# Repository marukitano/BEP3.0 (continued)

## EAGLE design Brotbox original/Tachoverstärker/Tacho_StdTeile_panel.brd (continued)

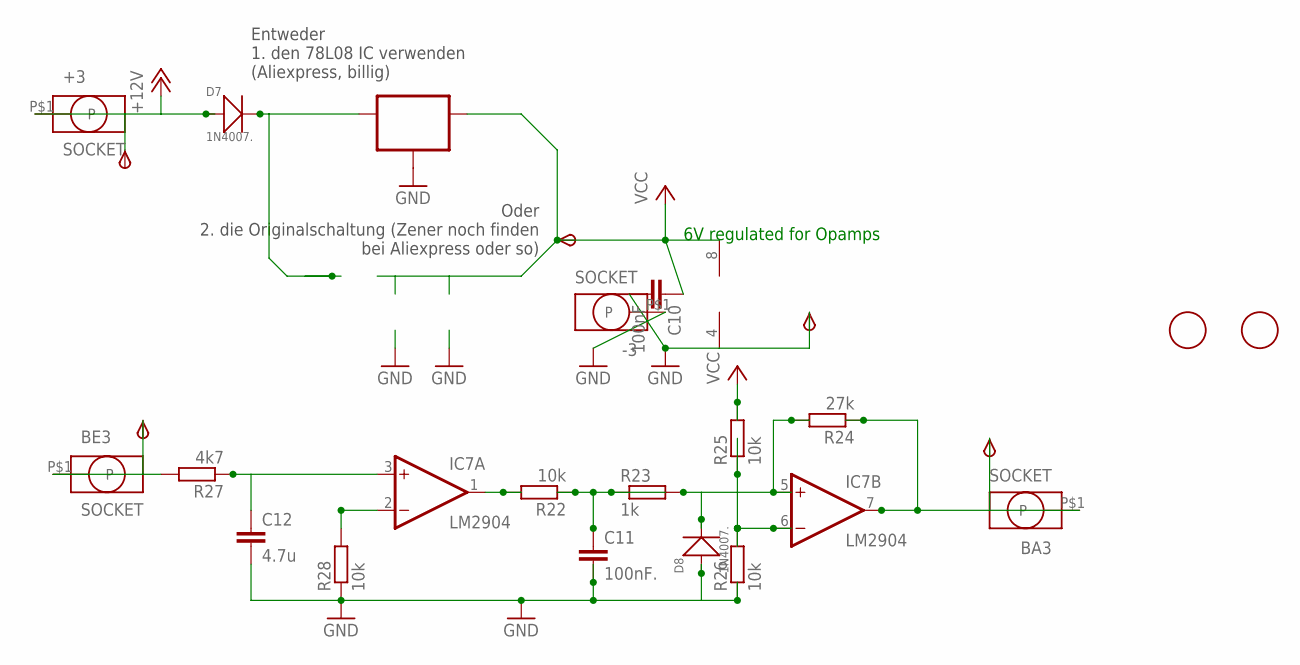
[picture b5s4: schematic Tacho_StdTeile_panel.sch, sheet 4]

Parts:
6V3: TPSB2.0; B2.0
+3: SOCKET; ID2.5MM
+12V3: TPSB2.0; B2.0
-3: SOCKET; ID2.5MM
AUS3: TPSB2.0; B2.0
BA3: SOCKET; ID2.5MM
BE3: SOCKET; ID2.5MM
C10: 100nF; C0805K
C11: 100nF.; C0805K
C12: 4.7u; C0805K
D7, D8: 1N4007.; DO-214AC
EIN3: TPSB2.0; B2.0
FID7, FID8: FIDUCIAL; FIDUCIAL_1MM
GND29: TPSB2.0; B2.0
IC7: LM2904; SO08
IC8: 78L06; SOT89_ROUND
R22, R25, R26, R28: 10k; R0805
R23: 1k; R0805
R24: 27k; R0805
R27: 4k7; R0805

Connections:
+12V: +3.P$1, +12V3.TP, D7.1 (+); also elsewhere on the board
+12V4: AUS3.TP, BA3.P$1, IC7.7 (OUT), R24.1
GND: -3.P$1, C10.2, C11.2, C12.2, D8.1 (+), GND29.TP, IC7.4 (V-), IC8.2 (GND), IC8.2@1 (GND), R26.1, R28.1; also elsewhere on the board
unnamed: IC7.2 (-IN), R28.2
unnamed: IC7.1 (OUT), R22.2
unnamed: C11.1, R22.1, R23.1
unnamed: D8.2 (-), IC7.5 (+IN), R23.2, R24.2
unnamed: IC7.6 (-IN), R25.1, R26.2
unnamed: BE3.P$1, EIN3.TP, R27.2
unnamed: C12.1, IC7.3 (+IN), R27.1
unnamed: D7.2 (-), IC8.3 (IN)
VCC: 6V3.TP, C10.1, IC7.8 (V+), IC8.1 (OUT), R25.2; also elsewhere on the board

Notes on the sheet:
6V regulated for Opamps
Entweder 1. den 78L08 IC verwenden (Aliexpress, billig)
Oder 2. die Originalschaltung (Zener noch finden bei Aliexpress oder so)

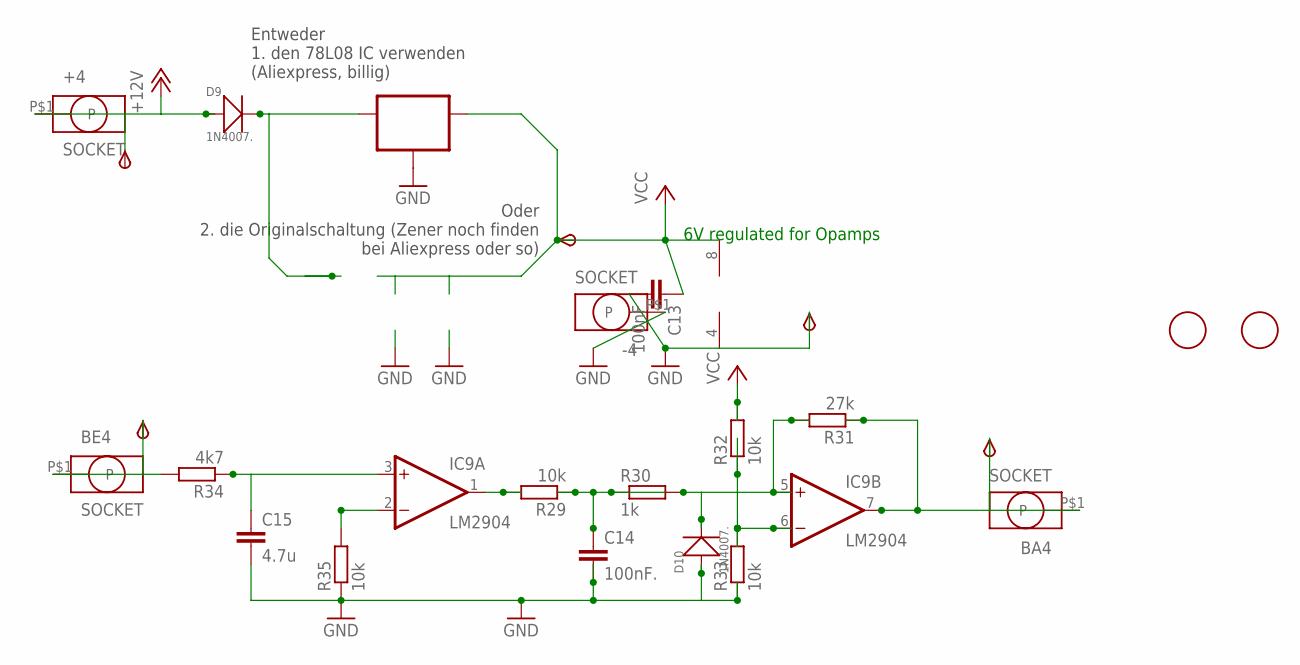
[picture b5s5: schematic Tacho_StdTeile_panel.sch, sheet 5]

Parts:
6V4: TPSB2.0; B2.0
+4: SOCKET; ID2.5MM
+12V4: TPSB2.0; B2.0
-4: SOCKET; ID2.5MM
AUS4: TPSB2.0; B2.0
BA4: SOCKET; ID2.5MM
BE4: SOCKET; ID2.5MM
C13: 100nF; C0805K
C14: 100nF.; C0805K
C15: 4.7u; C0805K
D9, D10: 1N4007.; DO-214AC
EIN4: TPSB2.0; B2.0
FID9, FID10: FIDUCIAL; FIDUCIAL_1MM
GND39: TPSB2.0; B2.0
IC9: LM2904; SO08
IC10: 78L06; SOT89_ROUND
R29, R32, R33, R35: 10k; R0805
R30: 1k; R0805
R31: 27k; R0805
R34: 4k7; R0805

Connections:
+12V: +4.P$1, +12V4.TP, D9.1 (+); also elsewhere on the board
+12V5: AUS4.TP, BA4.P$1, IC9.7 (OUT), R31.1
GND: -4.P$1, C13.2, C14.2, C15.2, D10.1 (+), GND39.TP, IC9.4 (V-), IC10.2 (GND), IC10.2@1 (GND), R33.1, R35.1; also elsewhere on the board
unnamed: IC9.2 (-IN), R35.2
unnamed: IC9.1 (OUT), R29.2
unnamed: C14.1, R29.1, R30.1
unnamed: D10.2 (-), IC9.5 (+IN), R30.2, R31.2
unnamed: IC9.6 (-IN), R32.1, R33.2
unnamed: BE4.P$1, EIN4.TP, R34.2
unnamed: C15.1, IC9.3 (+IN), R34.1
unnamed: D9.2 (-), IC10.3 (IN)
VCC: 6V4.TP, C13.1, IC9.8 (V+), IC10.1 (OUT), R32.2; also elsewhere on the board

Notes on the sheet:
6V regulated for Opamps
Entweder 1. den 78L08 IC verwenden (Aliexpress, billig)
Oder 2. die Originalschaltung (Zener noch finden bei Aliexpress oder so)

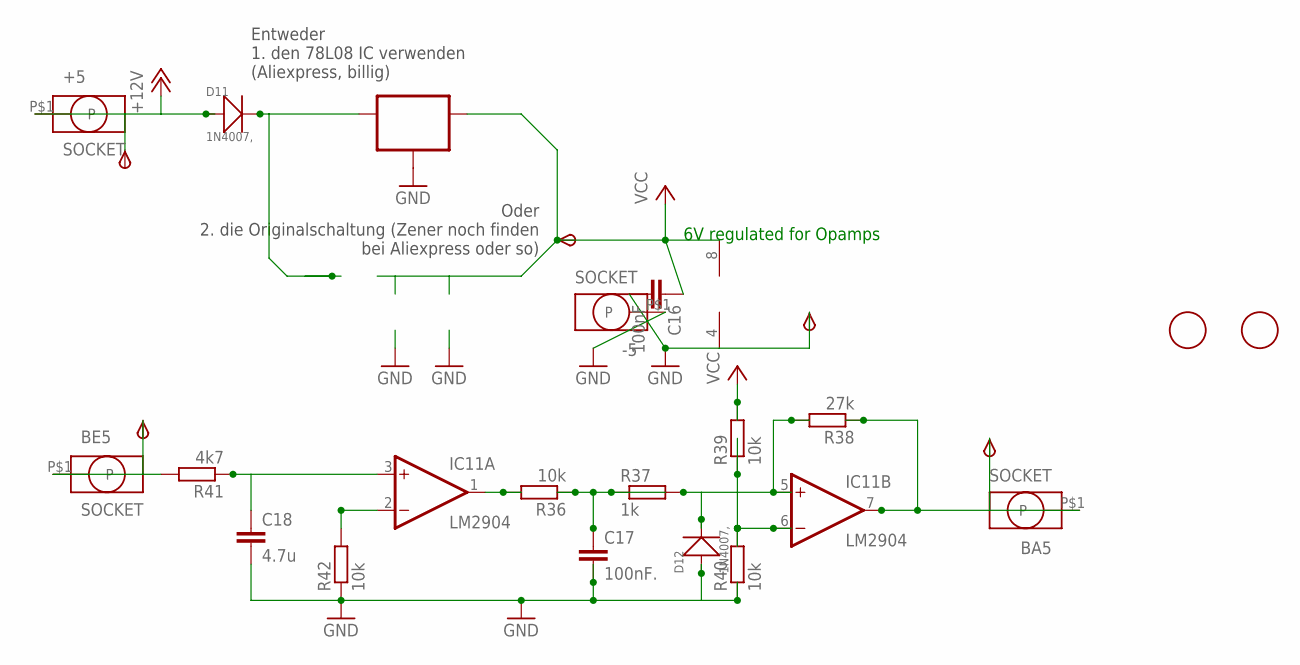
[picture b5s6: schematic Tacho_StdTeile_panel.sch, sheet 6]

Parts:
6V5: TPSB2.0; B2.0
+5: SOCKET; ID2.5MM
+12V5: TPSB2.0; B2.0
-5: SOCKET; ID2.5MM
AUS5: TPSB2.0; B2.0
BA5: SOCKET; ID2.5MM
BE5: SOCKET; ID2.5MM
C16: 100nF; C0805K
C17: 100nF.; C0805K
C18: 4.7u; C0805K
D11, D12: 1N4007,; DO-214AC
EIN5: TPSB2.0; B2.0
FID11, FID12: FIDUCIAL; FIDUCIAL_1MM
GND47: TPSB2.0; B2.0
IC11: LM2904; SO08
IC12: 78L06; SOT89_ROUND
R36, R39, R40, R42: 10k; R0805
R37: 1k; R0805
R38: 27k; R0805
R41: 4k7; R0805

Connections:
+12V: +5.P$1, +12V5.TP, D11.1 (+); also elsewhere on the board
+12V6: AUS5.TP, BA5.P$1, IC11.7 (OUT), R38.1
GND: -5.P$1, C16.2, C17.2, C18.2, D12.1 (+), GND47.TP, IC11.4 (V-), IC12.2 (GND), IC12.2@1 (GND), R40.1, R42.1; also elsewhere on the board
unnamed: IC11.2 (-IN), R42.2
unnamed: IC11.1 (OUT), R36.2
unnamed: C17.1, R36.1, R37.1
unnamed: D12.2 (-), IC11.5 (+IN), R37.2, R38.2
unnamed: IC11.6 (-IN), R39.1, R40.2
unnamed: BE5.P$1, EIN5.TP, R41.2
unnamed: C18.1, IC11.3 (+IN), R41.1
unnamed: D11.2 (-), IC12.3 (IN)
VCC: 6V5.TP, C16.1, IC11.8 (V+), IC12.1 (OUT), R39.2; also elsewhere on the board

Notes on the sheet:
6V regulated for Opamps
Entweder 1. den 78L08 IC verwenden (Aliexpress, billig)
Oder 2. die Originalschaltung (Zener noch finden bei Aliexpress oder so)

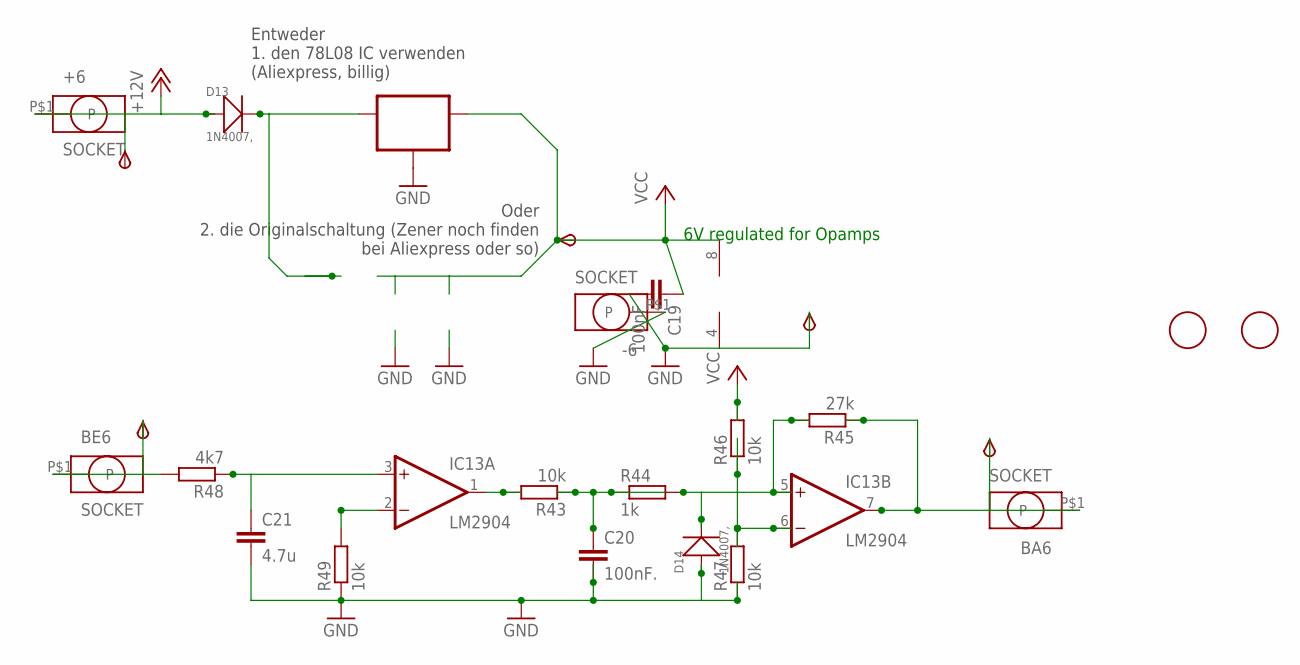
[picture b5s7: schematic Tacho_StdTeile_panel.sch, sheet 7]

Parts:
6V6: TPSB2.0; B2.0
+6: SOCKET; ID2.5MM
+12V6: TPSB2.0; B2.0
-6: SOCKET; ID2.5MM
AUS6: TPSB2.0; B2.0
BA6: SOCKET; ID2.5MM
BE6: SOCKET; ID2.5MM
C19: 100nF; C0805K
C20: 100nF.; C0805K
C21: 4.7u; C0805K
D13, D14: 1N4007,; DO-214AC
EIN6: TPSB2.0; B2.0
FID13, FID14: FIDUCIAL; FIDUCIAL_1MM
GND55: TPSB2.0; B2.0
IC13: LM2904; SO08
IC14: 78L06; SOT89_ROUND
R43, R46, R47, R49: 10k; R0805
R44: 1k; R0805
R45: 27k; R0805
R48: 4k7; R0805

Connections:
+12V: +6.P$1, +12V6.TP, D13.1 (+); also elsewhere on the board
+12V7: AUS6.TP, BA6.P$1, IC13.7 (OUT), R45.1
GND: -6.P$1, C19.2, C20.2, C21.2, D14.1 (+), GND55.TP, IC13.4 (V-), IC14.2 (GND), IC14.2@1 (GND), R47.1, R49.1; also elsewhere on the board
unnamed: IC13.2 (-IN), R49.2
unnamed: IC13.1 (OUT), R43.2
unnamed: C20.1, R43.1, R44.1
unnamed: D14.2 (-), IC13.5 (+IN), R44.2, R45.2
unnamed: IC13.6 (-IN), R46.1, R47.2
unnamed: BE6.P$1, EIN6.TP, R48.2
unnamed: C21.1, IC13.3 (+IN), R48.1
unnamed: D13.2 (-), IC14.3 (IN)
VCC: 6V6.TP, C19.1, IC13.8 (V+), IC14.1 (OUT), R46.2; also elsewhere on the board

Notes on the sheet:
6V regulated for Opamps
Entweder 1. den 78L08 IC verwenden (Aliexpress, billig)
Oder 2. die Originalschaltung (Zener noch finden bei Aliexpress oder so)

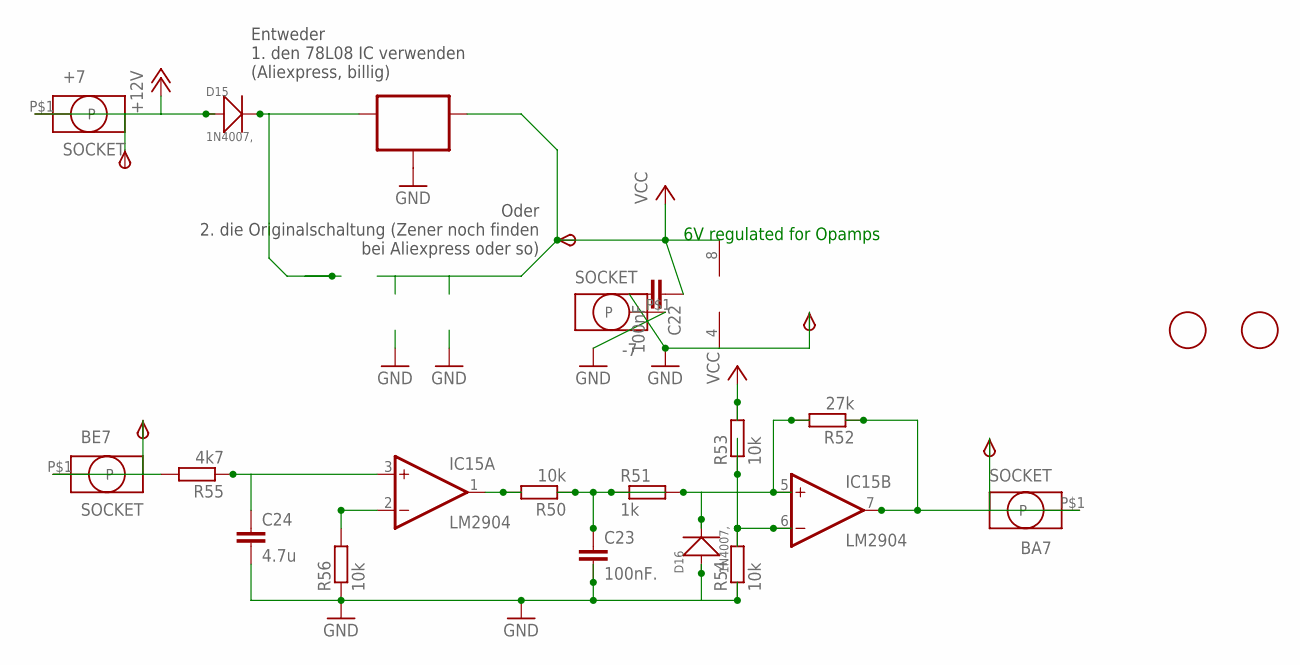
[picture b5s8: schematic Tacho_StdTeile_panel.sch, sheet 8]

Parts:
6V7: TPSB2.0; B2.0
+7: SOCKET; ID2.5MM
+12V7: TPSB2.0; B2.0
-7: SOCKET; ID2.5MM
AUS7: TPSB2.0; B2.0
BA7: SOCKET; ID2.5MM
BE7: SOCKET; ID2.5MM
C22: 100nF; C0805K
C23: 100nF.; C0805K
C24: 4.7u; C0805K
D15, D16: 1N4007,; DO-214AC
EIN7: TPSB2.0; B2.0
FID1, FID19: FIDUCIAL; FIDUCIAL_1MM
GND63: TPSB2.0; B2.0
IC15: LM2904; SO08
IC16: 78L06; SOT89_ROUND
R50, R53, R54, R56: 10k; R0805
R51: 1k; R0805
R52: 27k; R0805
R55: 4k7; R0805

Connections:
+12V: +7.P$1, +12V7.TP, D15.1 (+); also elsewhere on the board
+12V8: AUS7.TP, BA7.P$1, IC15.7 (OUT), R52.1
GND: -7.P$1, C22.2, C23.2, C24.2, D16.1 (+), GND63.TP, IC15.4 (V-), IC16.2 (GND), IC16.2@1 (GND), R54.1, R56.1; also elsewhere on the board
unnamed: IC15.2 (-IN), R56.2
unnamed: IC15.1 (OUT), R50.2
unnamed: C23.1, R50.1, R51.1
unnamed: D16.2 (-), IC15.5 (+IN), R51.2, R52.2
unnamed: IC15.6 (-IN), R53.1, R54.2
unnamed: BE7.P$1, EIN7.TP, R55.2
unnamed: C24.1, IC15.3 (+IN), R55.1
unnamed: D15.2 (-), IC16.3 (IN)
VCC: 6V7.TP, C22.1, IC15.8 (V+), IC16.1 (OUT), R53.2; also elsewhere on the board

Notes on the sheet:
6V regulated for Opamps
Entweder 1. den 78L08 IC verwenden (Aliexpress, billig)
Oder 2. die Originalschaltung (Zener noch finden bei Aliexpress oder so)

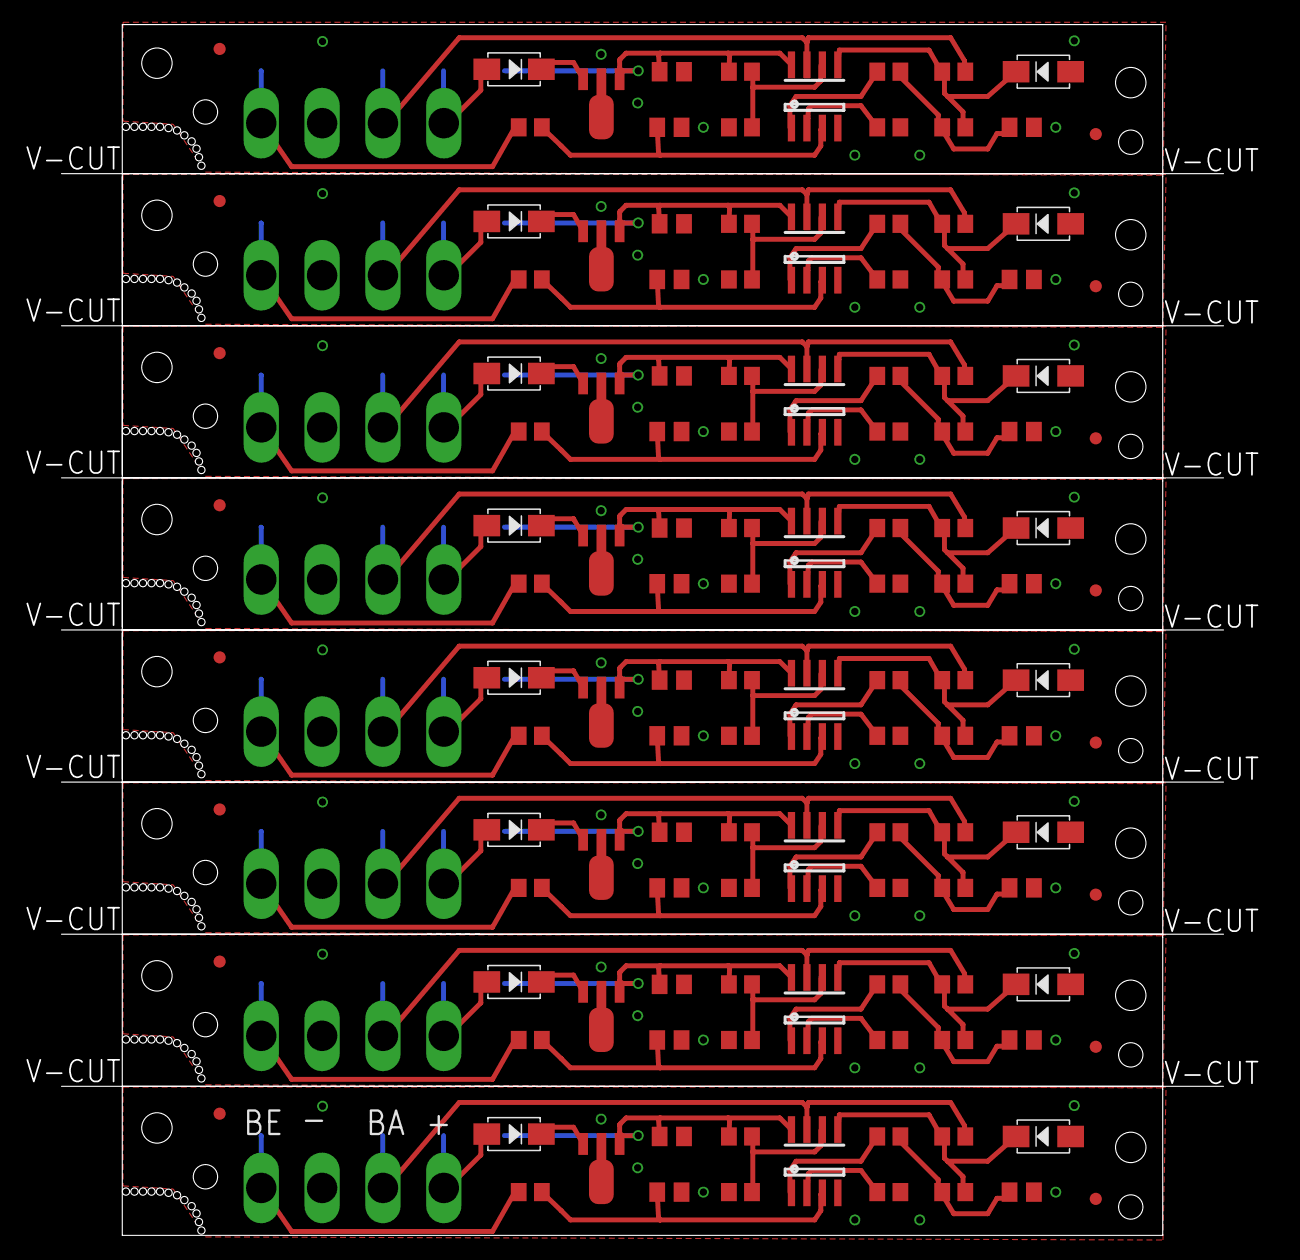
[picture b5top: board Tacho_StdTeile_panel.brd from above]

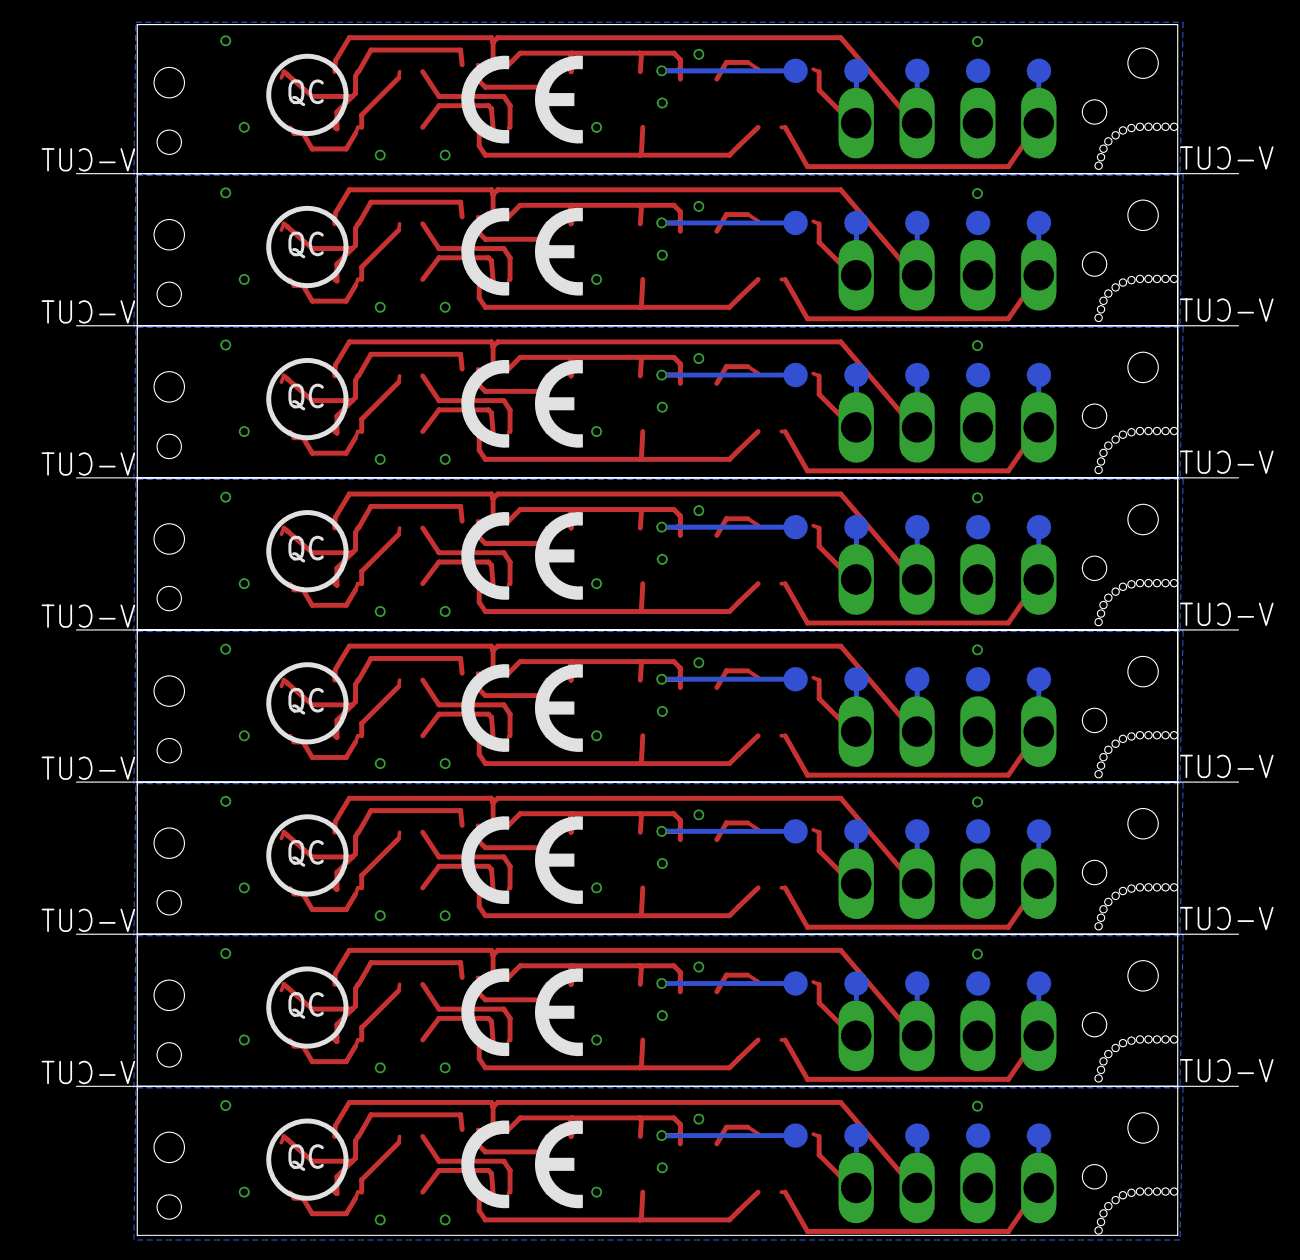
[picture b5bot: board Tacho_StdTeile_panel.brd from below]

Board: 2 copper layers, 85.5 x 99.5 mm, 208 parts (48 on the bottom side), 75 nets.

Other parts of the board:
U$1, U$2, U$3, U$4, U$5, U$6, U$7, U$8: CE_10.00

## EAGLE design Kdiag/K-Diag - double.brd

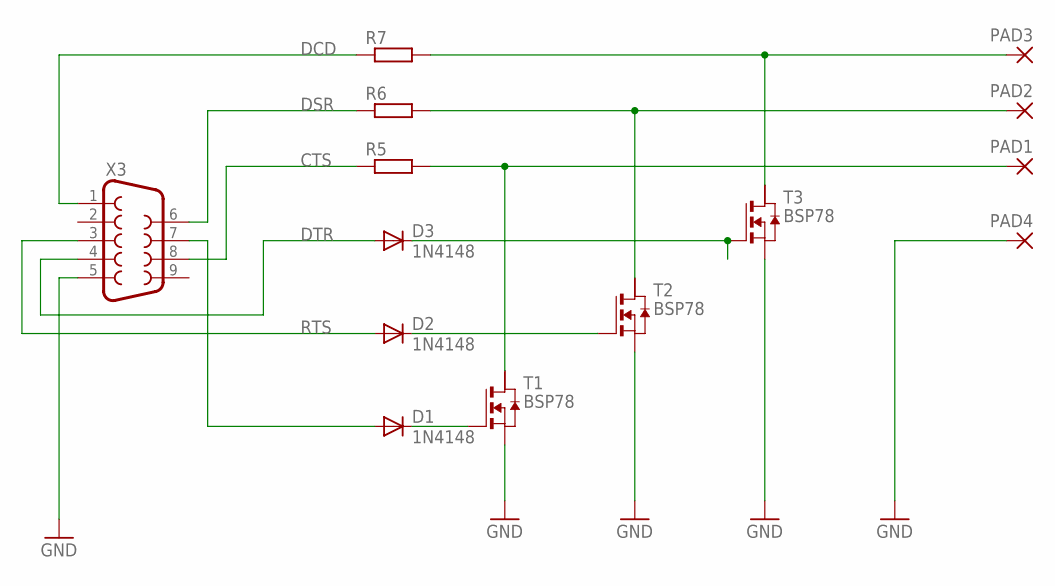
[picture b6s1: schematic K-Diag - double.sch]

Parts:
D1, D2, D3: 1N4148; DO214AC
PAD1, PAD2, PAD3, PAD4: 2,54/0,8
R5, R6, R7: R-EU_R0805; R0805
T1, T2, T3: BSP78; SOT223
X3: F09D

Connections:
CTS: R5.1, X3.8
DCD: R7.1, X3.1
DSR: R6.1, X3.6
DTR: D3.A, X3.4
GND: PAD4.1, T1.3 (S), T2.3 (S), T3.3 (S), X3.5
unnamed: D3.C, T3.1 (G)
unnamed: D2.C, T2.1 (G)
unnamed: D1.C, T1.1 (G)
unnamed: PAD1.1, R5.2, T1.2 (D)
unnamed: PAD2.1, R6.2, T2.2 (D)
unnamed: PAD3.1, R7.2, T3.2 (D)
unnamed: D1.A, X3.7
RTS: D2.A, X3.3

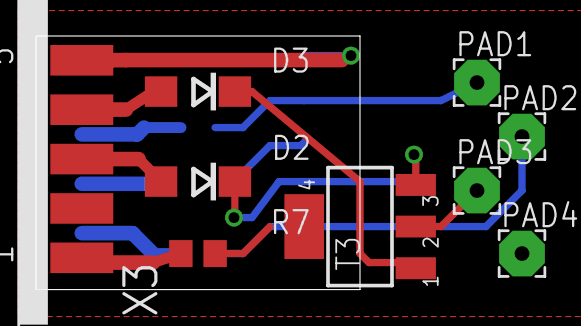
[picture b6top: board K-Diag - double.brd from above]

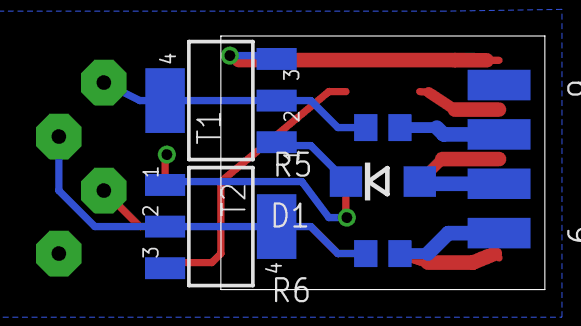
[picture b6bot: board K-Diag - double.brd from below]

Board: 2 copper layers, 14 parts (5 on the bottom side), 13 nets.
